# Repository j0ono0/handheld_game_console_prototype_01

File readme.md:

# Handheld game console and Arduino game

The motivation and goal of this project was primarily as an excuse to try and design my first PCB. Choosing a handheld game console made an appealing form on several points:

- Has enough wiring to be an interesting, but achievable with no prior experience
- Makes a useful progression from a breadboard prototype
- Results in an artifact that has broad appeal and is fun showing off to tech, and non-tech, friends alike  

To fully realise success I needed a game to run on the hardware. To Achieve this requirement I chose to appropriate the key game mechanic of Sokoban (designed in 1981 by Hiroyuki Imabayashi, and first published in December 1982 [[wikipedia](https://en.wikipedia.org/wiki/Sokoban)]).

## Hardware

Having a [Teensy 4](https://www.pjrc.com/store/teensy40.html) and [TFT screen](https://www.pjrc.com/store/display_ili9341_touch.html) on hand set some initial design constraints. The microcontroller has generous limitations and made for fast firmware development without the need for much attention to optimisation.

The initial wiring was tested on a bread-board with microcontroller and screen communicating via SPI. Several input buttons were multiplexed, not due to lack of gpio pins, but simply to try out a technique new to me. At this point the hardware worked reliably but was somewhat unwieldy to press buttons and move around my desk whilst developing the game. 

The screen module includes touch input and an SD card reader. In the spirit of making a fully-featured development device I decided to enable these additional components. Once connected on the bread-board the hardware ceased to work reliably. Testing individually each did work correctly making for a hopeful outlook. I decided to forge ahead and include these components after ponder failure/fix scenarios:

- Bread-board/wiring issue - Issue will be fixed with PCB wiring
- Faulty hardware - I can cut traces on the PCB effectively 'removing' components
- Firmware error - Not initialising components or changing code/libraries should resolve errors

With a somewhat working bread-board prototype I moved onto designing a PCB with [KiCad](https://www.kicad.org/). Component placement was dictated largely by functional requirements of being a hand-held game console. Routing wires became a puzzle that included reconfiguring pin functions of the microcontroller for most efficient outcomes. Amongst advice I gained during this process was to print out and place parts before finalising the design which proved to be golden as I picked up a measurement error in a footprint I created. I also created some simple graphics for the silkscreen to test that process.

Prior to commencing the PCB design I selected [PCBWay](https://www.pcbway.com/) for fabrication. My choice was primarily driven by price and website usability/clarity. Opting for the cheapest configuration (I had no real confidence this project would work out) guided maximum PCB size and some other KiCad settings to meet fabrication requirements. On completion of the design, submission of files was straight forward with good documentation on the PCBWay website to guide the process. Fabrication and delivery was _fast_, 5 day turn-a-round with the vast majority of that time being transit to/through Australia. The novelty of holding my own, high quality and professionally manufactured, PCB is still exciting a few weeks later as I write-up this project summary. The PCB looks excellent including the silkscreen test graphics which is encouraging to try out some more demanding artwork for the next project.

Assembly on the PCB was uncomplicated with only through hole components and all parts fitting as intended. Once assembled SPI reliability issues vanished with all components working perfectly. I assume controlling x3 SPI devices was pushing the capabilities of my bread-board. Power and portability was resolved by taping a small battery bank to the reverse side and providing power via the USB plug. This made for a fun prototype to show off on-the-go and easy to swap for tethered development at my desk.

## Firmware

Goals for this section of the project were less defined than the hardware - Something fun to show off and achievable to create. I have a 'secret' ongoing project of creating a roguelike and would very much like it to run on a handheld console. With several attempts of this game genre for desktop under my belt - all of them failures of varying degrees - I decided to set some further constraints around what a 'minimum viable product' might look like. The result is my homage to Sokoban (see intro for details). The code is total overkill for the task at hand but with the thought it might be the groundwork for a more complex roguelike game.

The project utilises the Arduino environment which streamlines access to libraries, interfacing with hardware, and compiling/uploading. Whilst Arduino is essentially C++, I've attempted to primarily write in C compatible code as practice for developing for more restricted hardware devices. 

In the course of processing graphics for embedding into the game I wrote a hand-full of Python scripts. These are a work-in-progress as I experiment and streamline how I create graphical assets (sprites, level maps, and background tiles) and process them for embedding into the code.

At the time of writing this the game is fully functional with 3 levels. The user interface includes buttons to reset, skip levels, plus display a demo art screen. The latter as a talking point for where the graphics may go when showing off the project.

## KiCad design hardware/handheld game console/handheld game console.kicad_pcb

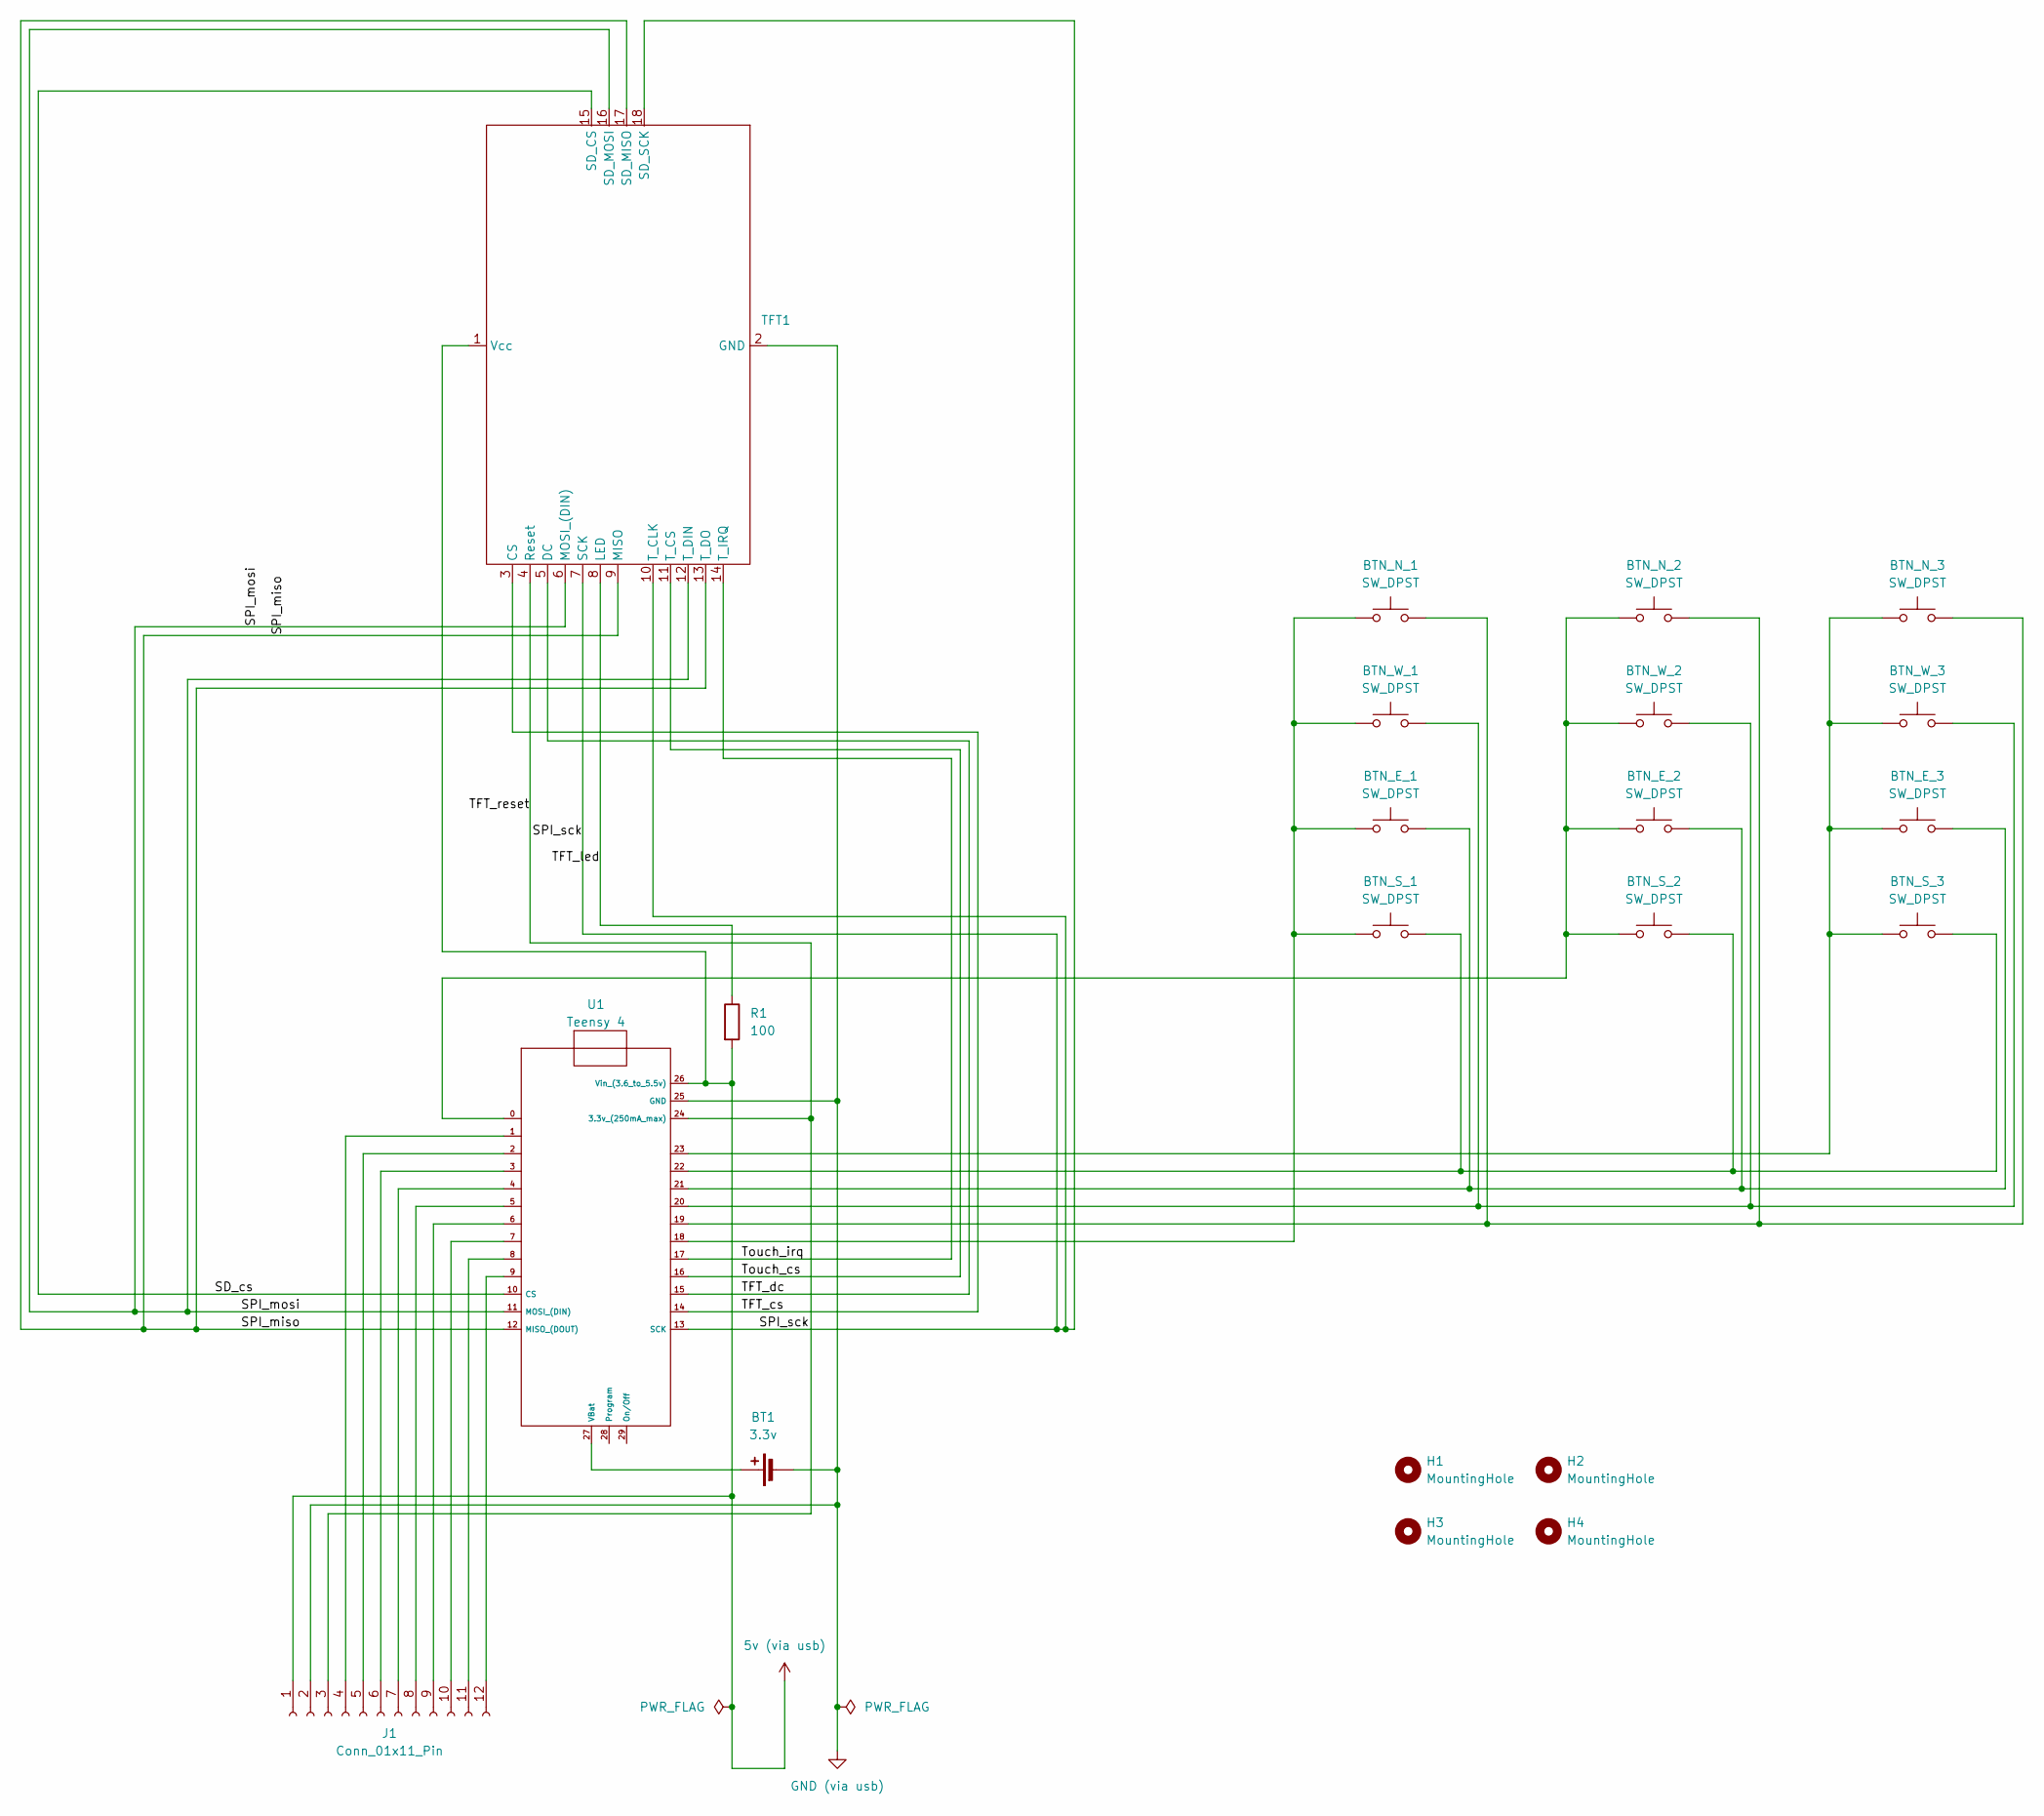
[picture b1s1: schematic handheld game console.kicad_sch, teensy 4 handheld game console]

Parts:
BT1: 3.3v; Battery_Holder
BTN_E_1, BTN_E_2, BTN_E_3: SW_DPST; tactile switch 6.5 x 4.5
BTN_N_1, BTN_N_2, BTN_N_3: SW_DPST; tactile switch 6.5 x 4.5
BTN_S_1, BTN_S_2, BTN_S_3: SW_DPST; tactile switch 6.5 x 4.5
BTN_W_1, BTN_W_2, BTN_W_3: SW_DPST; tactile switch 6.5 x 4.5
H1, H2, H3, H4: MountingHole; MountingHole_2.2mm_M2
J1: Conn_01x11_Pin; PinHeader_1x12_P2.54mm_Vertical
R1: 100; R_Axial_DIN0207_L6.3mm_D2.5mm_P7.62mm_Horizontal
TFT1: TFT_touchscreen_ili9341_controller_chip
U1: Teensy 4; teensy_4

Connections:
5v (via usb): J1.1, R1.2, TFT1.1 (Vcc), U1.26 (Vin_(3.6_to_5.5v))
/SD_cs: TFT1.15 (SD_CS), U1.10 (CS)
/SPI_miso: TFT1.9 (MISO), TFT1.13 (T_DO), TFT1.17 (SD_MISO), U1.12 (MISO_(DOUT))
/SPI_mosi: TFT1.6 (MOSI_(DIN)), TFT1.12 (T_DIN), TFT1.16 (SD_MOSI), U1.11 (MOSI_(DIN))
/SPI_sck: TFT1.7 (SCK), TFT1.10 (T_CLK), TFT1.18 (SD_SCK), U1.13 (SCK)
/TFT_cs: TFT1.3 (CS), U1.14
/TFT_dc: TFT1.5 (DC), U1.15
/TFT_led: R1.1, TFT1.8 (LED)
/TFT_reset: J1.3, TFT1.4 (Reset), U1.24 (3.3v_(250mA_max))
/Touch_cs: TFT1.11 (T_CS), U1.16
/Touch_irq: TFT1.14 (T_IRQ), U1.17
GND (via usb): BT1.2 (-), J1.2, TFT1.2 (GND), U1.25 (GND)
unnamed: BT1.1 (+), U1.27 (VBat)
unnamed: BTN_E_1.1, BTN_N_1.1, BTN_S_1.1, BTN_W_1.1, U1.18
unnamed: BTN_E_1.2, BTN_E_2.2, BTN_E_3.2, U1.21
unnamed: BTN_E_2.1, BTN_N_2.1, BTN_S_2.1, BTN_W_2.1, U1.0
unnamed: BTN_E_3.1, BTN_N_3.1, BTN_S_3.1, BTN_W_3.1, U1.23
unnamed: BTN_N_1.2, BTN_N_2.2, BTN_N_3.2, U1.19
unnamed: BTN_S_1.2, BTN_S_2.2, BTN_S_3.2, U1.22
unnamed: BTN_W_1.2, BTN_W_2.2, BTN_W_3.2, U1.20
unnamed: J1.4, U1.1
unnamed: J1.5, U1.2
unnamed: J1.6, U1.3
unnamed: J1.7, U1.4
unnamed: J1.8, U1.5
unnamed: J1.9, U1.6
unnamed: J1.10, U1.7
unnamed: J1.11, U1.8
unnamed: J1.12, U1.9

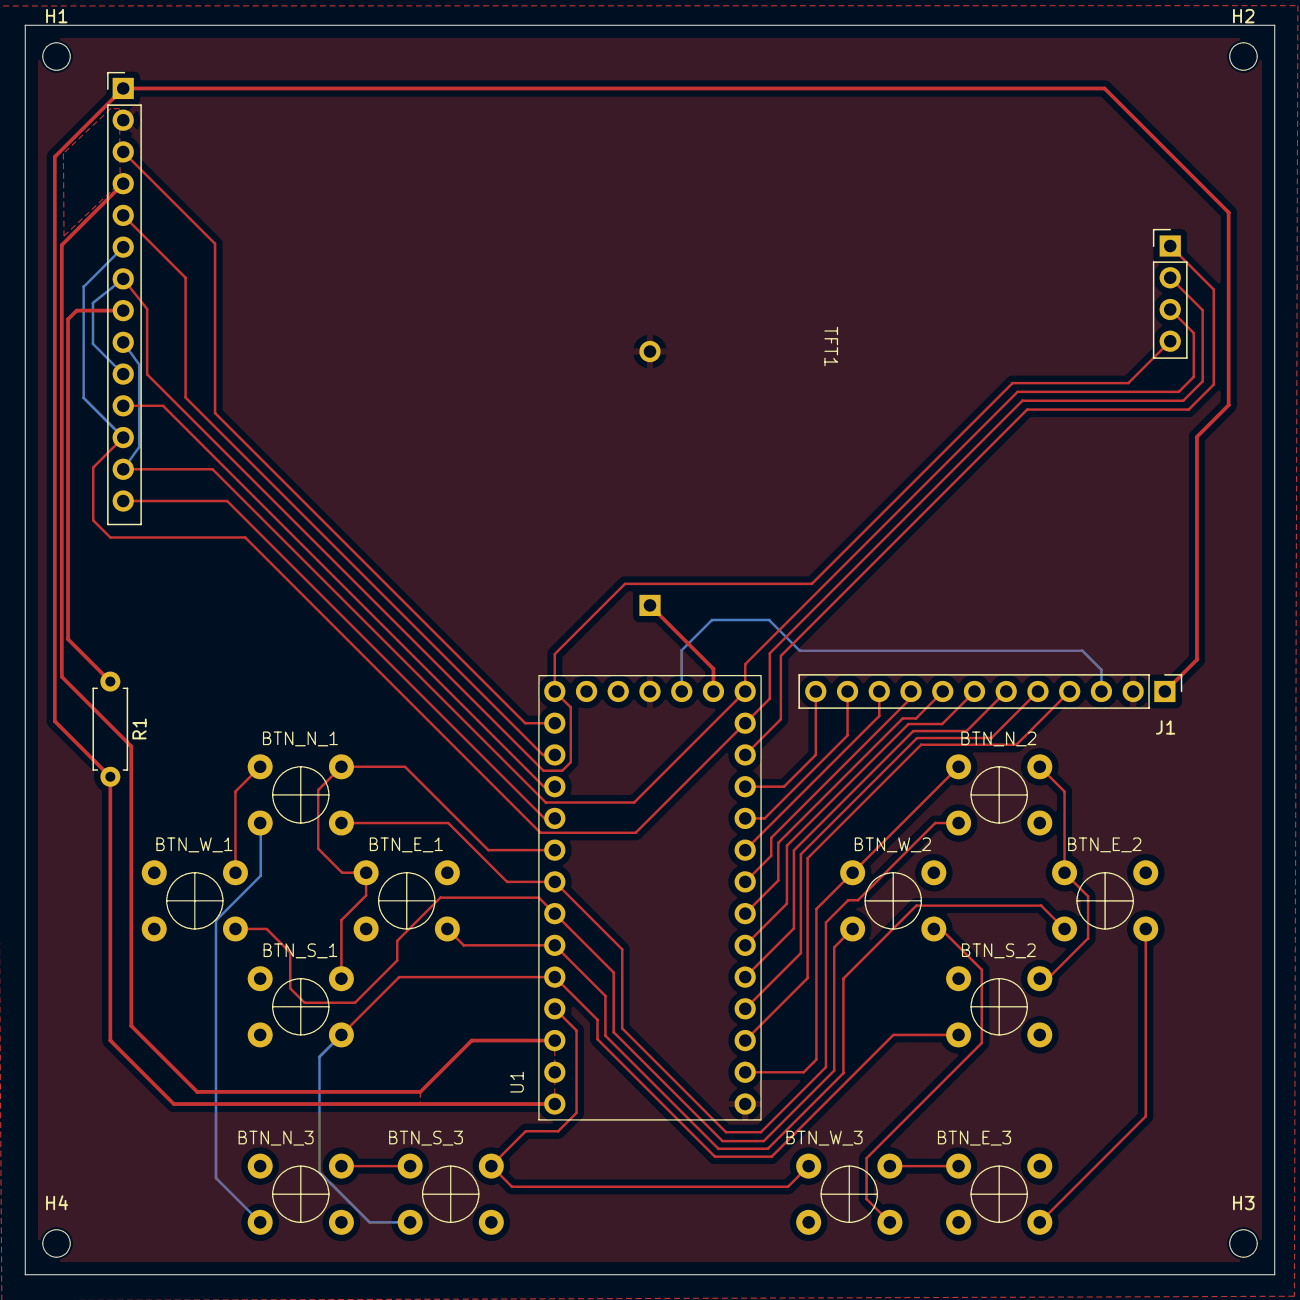
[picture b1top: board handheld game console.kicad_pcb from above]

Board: 2 copper layers, 100.0 x 100.0 mm, 21 parts (1 on the bottom side), 29 nets.

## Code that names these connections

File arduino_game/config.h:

#ifndef game_config_h
#define game_config_h

// SPI hardware pins
#define TFT_CS 14
#define SD_CS 10
#define XPT_CS 16 // touch cs

#define TFT_DC 15


// #define XPT_IRQ  17


#define PIN_MP_PWR_1 18
#define PIN_MP_PWR_2 0
#define PIN_MP_PWR_3 23

#define PIN_MP_N 19
#define PIN_MP_W 20
#define PIN_MP_E 21
#define PIN_MP_S 22


/*
    Note:
    Terrain grid size is chosen for more effecient graphics.
    Env grid at x2 terrain size makes for better UI.

    ?? Generally everything should be expressed in
    env-grid leaving terrain-grid for lower level functions. ??
*/

#define SCREEN_WIDTH 320
#define SCREEN_HEIGHT 240

// Terrain tiles are split into a grid.
// Each cell of this 'terrain grid' is 8x8 pixels
#define TERRAIN_WIDTH 40
#define TERRAIN_HEIGHT 30
#define TERRAIN_UNIT 8

// Entities are tracked within the an 'environment grid'.
// These grid cells are 16x16 pixels.
#define ENV_WIDTH 20
#define ENV_HEIGHT 15
#define ENV_UNIT 16

#define COLOR_FLOOR 0xbe5c
#define COLOR_FLOOR_TARGET 0x9d9b
#define COLOR_BOX 0xc4c7
#define COLOR_BOX_ACTIVE 0xfb42
#define COLOR_WALL 0x8494
#define COLOR_PLAYER 0x3c04
#define COLOR_WATER 0x25b9

#define COLOR_TRANSPARENT 0x07e0

#define MAX_ENTITIES 100

#endif

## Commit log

2024-06-28 basic working game parts.
2024-06-29 save point before new linked list implementation.
2024-06-29 working linked list location check
2024-06-29 working linked list version (might have memory bug!)
2024-06-30 fixed destroyAssets
2024-06-30 remove unused functions
2024-06-30 updated draw functions
2024-06-30 implemented plr sprite
2024-07-01 track terrain and asset location by array
2024-07-01 refactor/tidy
2024-07-02 update plr sprite
2024-07-03 update memory mangement and sprite creation
2024-07-04 update sprites
2024-07-08 user buffer for drawing to tft
2024-07-09 condense sprite into single sheet
2024-07-10 revised map data
2024-07-10 draw new map data to screen
2024-07-11 move all game mechanics to engine
2024-07-11 tile LUT
2024-07-14 update tile graphics
2024-07-14 convert to 8x8 px terrain tiles
2024-07-15 tween plr movement.
2024-07-15 basic walk cycle for plr
2024-07-16 overlapping terrain tiles
2024-07-17 update walk animation function
2024-07-18 animate on game loop -proof of concept
2024-07-19 tidy up
2024-07-21 wip - render terrain by px rect
2024-07-22 revised screen draw - entire screen refresh
2024-07-22 update entity drawing
2024-07-23 update sprite animation. udpate success criteria
2024-07-25 add UI keypress queue
2024-07-25 update main loop and bug fixes
2024-08-07 update graphics
2024-08-08 update graphics. update UI input.
2024-08-08 add entities/sprites
2024-08-12 update splash screens
2024-08-14 initial indexed color for terrain
2024-08-15 broken mystery!
2024-08-15 udpate project structure
2024-08-15 update gitignore
2024-08-15 update tools. game working again! x2 levels
2024-08-15 update gameSolution to include powerconverters
2024-08-15 implement colour LUTs for terrain
2024-08-16 enable cycling through levels and screens
2024-08-22 recode sprites
2024-08-22 updated sprites
2024-08-26 enabling behaviours
2024-08-26 refactor behaviour and interaction code
2024-08-26 move resources access via arduino_game.ino
2024-08-26 code tidy up
2024-08-27 centralise animation clock
2024-08-27 prep for pull
2024-08-28 animated sprite attempt (fail)
2024-08-28 update sprite animation system
2024-08-28 update animation system (WIP)
2024-08-29 assign animation control to behaviours
2024-08-29 add more sprites
2024-08-30 add variable frame rates for sprites.
2024-09-18 add hardware
2024-09-18 enable color palette setting in EnvSpec.
2024-09-24 add readme. tidy up
2024-10-03 new level. updated readme
2024-10-03 add MIT licence
